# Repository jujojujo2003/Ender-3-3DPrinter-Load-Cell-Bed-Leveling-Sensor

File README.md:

# Ender-3-3DPrinter-Load-Cell-Bed-Leveling-Sensor
 This is a Load Cell based bed leveling sensor that should mount onto any vertical MGN12H gantry
 It uses
 * [ADS1235 ADC](https://www.digikey.com/en/products/detail/texas-instruments/ADS1235QWRHMRQ1/11308865) due to its 24-bit ADC, 7.2k sampling rate, 128x PGA gain.
 * [RP2040 MCU](https://www.raspberrypi.com/products/rp2040/) to do all the processing
 * [500g TAL 221 Loadcell](https://cdn.sparkfun.com/assets/9/9/a/f/3/TAL221.pdf) due to its compact nature. My gantry weighs around 250g. So make sure to select appropriate loadcell based on your gantry's weight so as to not saturate the loadcell.

My 3d printer is an Ender-3 with [3dFused's linear rail kit](https://3dfused.com/product/xaxis235/) and it perfectly works with that.

## PCB

You can order this PCB on [OSHPark](https://oshpark.com/shared_projects/gbeaSpQu).
Alternatively, the KiCad Schematic is available on [github](https://github.com/jujojujo2003/MGN12H-3DPrinter-LoadCell-BedLevelingSensor/tree/main/PCB) and the [Digikey parts list here](https://github.com/jujojujo2003/MGN12H-3DPrinter-LoadCell-BedLevelingSensor/blob/main/PCB/LoadCellDigikeyParts.csv)

<TBD> Source code and mounting bracket

## Code

The Arduino IDE code is available [here](https://github.com/jujojujo2003/MGN12H-3DPrinter-LoadCell-BedLevelingSensor/tree/main/Code). 
* Install [Arduino IDE](https://www.arduino.cc/en/software)
* Install the following Arduino Libraries
  * [PioSPI](https://www.arduino.cc/reference/en/libraries/piospi/)
  * [Adafruit NeoPixel](https://www.arduino.cc/reference/en/libraries/adafruit-neopixel/)
  * [RunningAverage](https://www.arduino.cc/reference/en/libraries/runningaverage/)
* Try compiling the binary

Alternatively, you can flash the [precompiled binary](https://github.com/jujojujo2003/MGN12H-3DPrinter-LoadCell-BedLevelingSensor/releases/tag/release)

## Normal Operation

* If everything is wired correctly, as soon as you power on, the LED should be RED for a few seconds and then turn off. If it flashes red, then there is an error. Try connecting the USB port and check the debug message printed to serial. 

* When the sensor is probing, the LED should turn blue to indicate that it is probing and turn green for a short while when triggered.

## Tuning
[DELTA_FOR_TRIGGER](https://github.com/jujojujo2003/MGN12H-3DPrinter-LoadCell-BedLevelingSensor/blob/main/Code/bedlevelRp2040ADS1235.ino#L8) is the main tuning variable that controls the sensitivity of the probe.

* Typically, set DELTA_FOR_TRIGGER to a low value like 1-2 and set `is_probing = true`
* Reset your printer and as soon as it starts, the LED should be BLUE. Note that it might get triggers very easily and turn green since the threshold above is low.
* Keep the filament wire into the extruder tight and try to extrude filament or move the printer head and keep bumping up DELTA_FOR_TRIGGER till such motions don't trigger.
* Now the probe will only trigger for probing motions

## Z-Probe Repeatability Test

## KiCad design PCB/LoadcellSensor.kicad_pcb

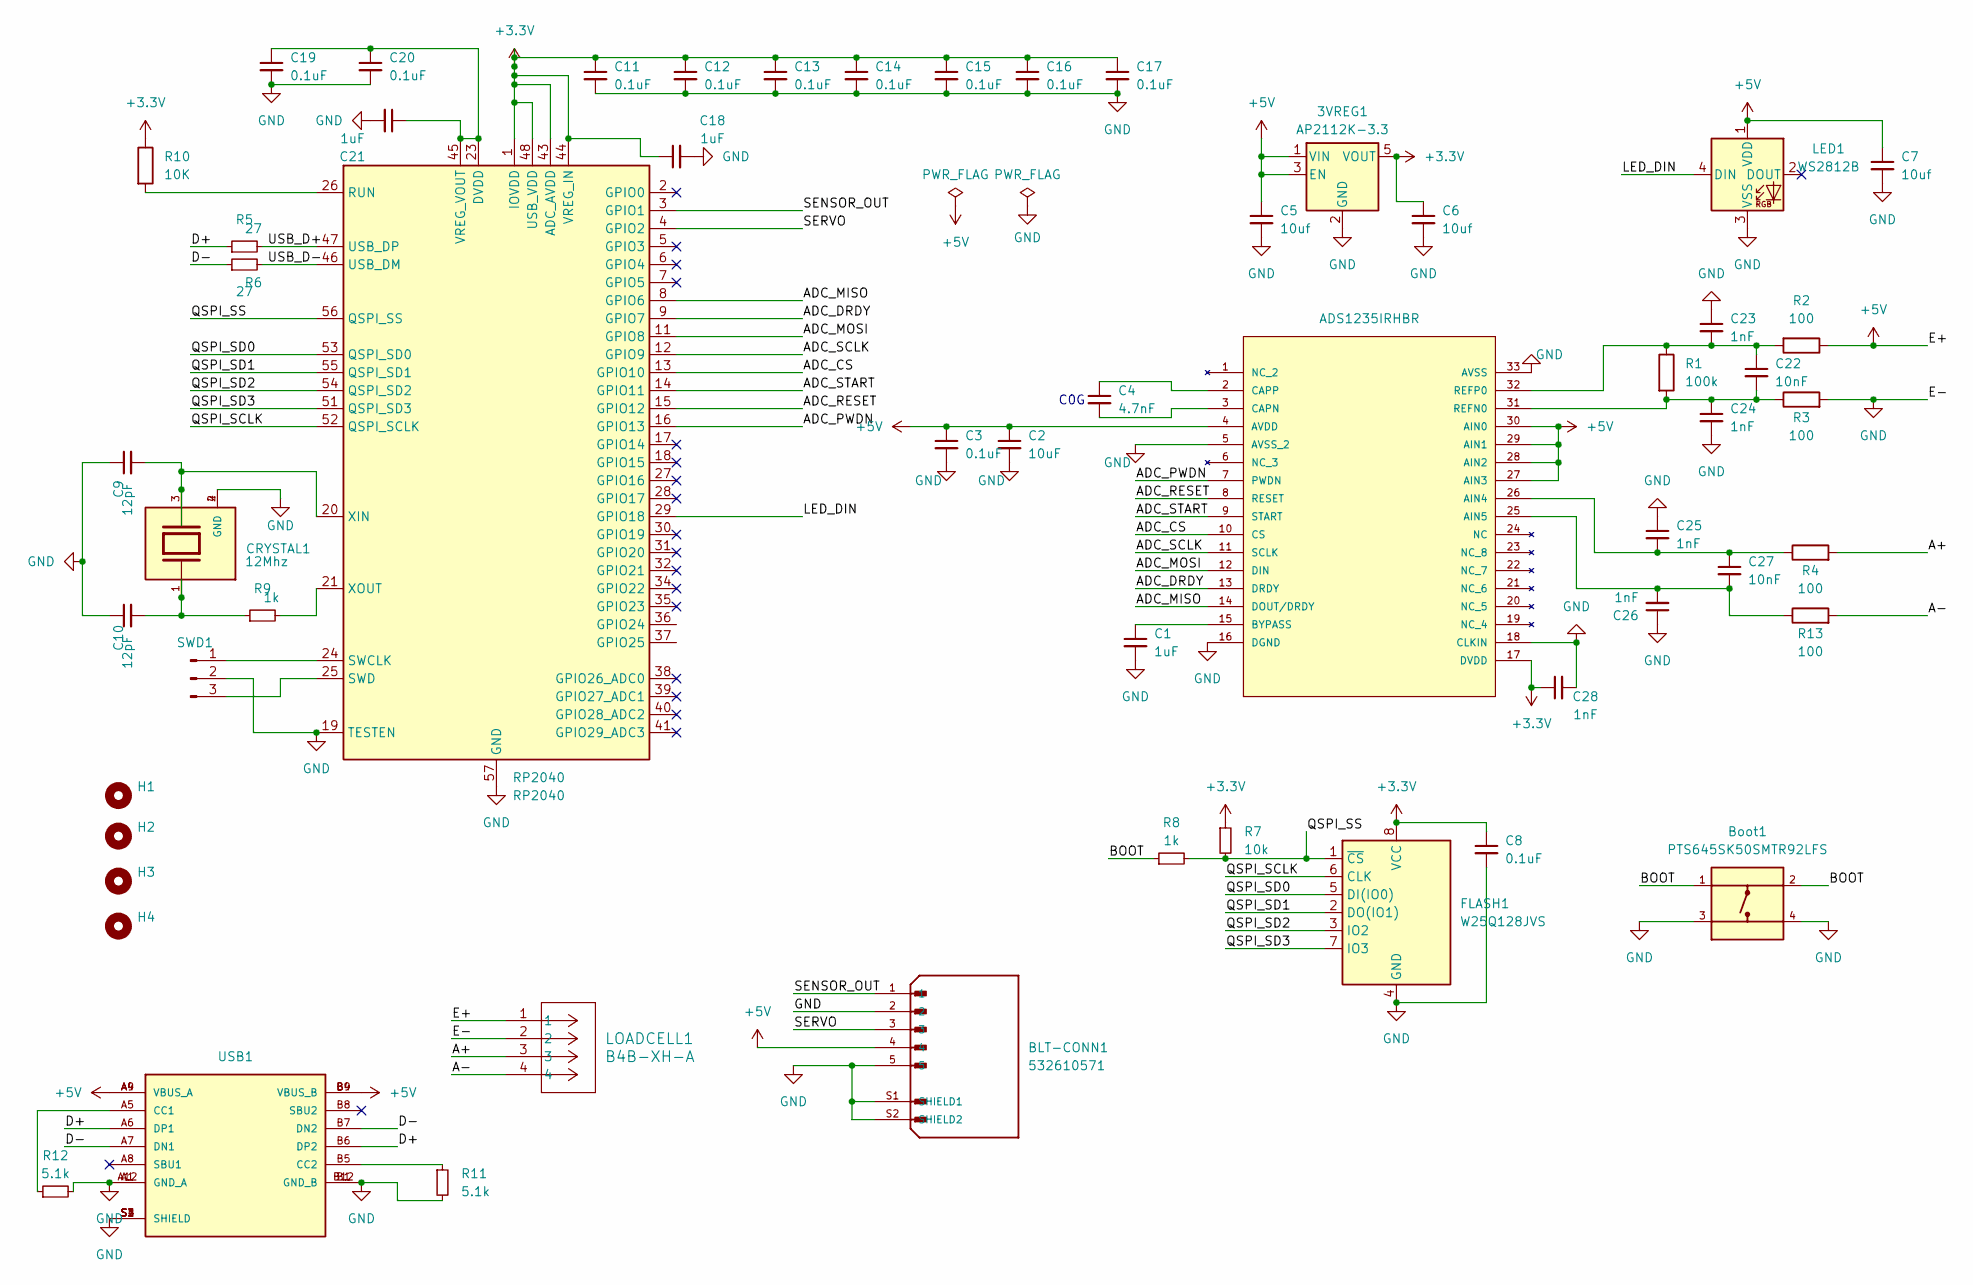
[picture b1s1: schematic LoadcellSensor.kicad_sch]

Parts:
3VREG1: AP2112K-3.3; SOT-23-5; DigiKey_Part_Number AP2112K-3.3TRG1DICT-ND
BLT-CONN1: 532610571; MOLEX_532610571; PARTREV J; DigiKey_Part_Number WM7623CT-ND
Boot1: PTS645SK50SMTR92LFS; SW_PTS645SK50SMTR92LFS; DigiKey_Part_Number CKN9087TR-ND
C1, C18, C21: 1uF; C_0805_2012Metric_Pad1.18x1.45mm_HandSolder; DigiKey_Part_Number 311-3498-1-ND
C2: 10uF; C_0805_2012Metric_Pad1.18x1.45mm_HandSolder; DigiKey_Part_Number 399-C0805C106J8RACAUTO7210CT-ND
C3, C8, C11, C12, C13, C14, C15, C16, C17, C19, C20: 0.1uF; C_0805_2012Metric_Pad1.18x1.45mm_HandSolder; DigiKey_Part_Number 311-1858-1-ND
C4: 4.7nF; C_0805_2012Metric_Pad1.18x1.45mm_HandSolder; DigiKey_Part_Number 399-C0805C472F5GEC7800CT-ND
C5, C6, C7: 10uf; C_0805_2012Metric_Pad1.18x1.45mm_HandSolder; DigiKey_Part_Number 399-C0805C106J8RACAUTO7210CT-ND
C9, C10: 12pF; C_0805_2012Metric_Pad1.18x1.45mm_HandSolder; DigiKey_Part_Number 399-C0805C120C5GAC7800CT-ND
C22, C27: 10nF; C_0805_2012Metric_Pad1.18x1.45mm_HandSolder; DigiKey_Part_Number 399-C0805C103J5GEC7800CT-ND
C23, C24, C25, C26, C28: 1nF; C_0805_2012Metric_Pad1.18x1.45mm_HandSolder; DigiKey_Part_Number 399-17883-1-ND
CRYSTAL1: 12Mhz; XTAL_ABM3B-12.000MHZ-12-N2Y-T; PARTREV 08.25.15; DigiKey_Part_Number 535-14827-1-ND
FLASH1: W25Q128JVS; SOIC-8_5.23x5.23mm_P1.27mm; DigiKey_Part_Number W25Q128JVSIQCT-ND
H1, H2, H3, H4: MountingHole; MountingHole_3.5mm
LED1: WS2812B; LED_WS2812B_PLCC4_5.0x5.0mm_P3.2mm; DigiKey_Part_Number WS2812B
LOADCELL1: B4B-XH-A; JST_XH_B4B-XH-A_1x04_P2.50mm_Vertical
R1: 100k; R_0805_2012Metric_Pad1.20x1.40mm_HandSolder; DigiKey_Part_Number 13-RC0805FR-13100KLCT-ND
R2, R3, R4, R13: 100; R_0805_2012Metric_Pad1.20x1.40mm_HandSolder; DigiKey_Part_Number 311-100CRCT-ND
R5, R6: 27; R_0805_2012Metric_Pad1.20x1.40mm_HandSolder; DigiKey_Part_Number 311-27.0CRCT-ND
R7: 10k; R_0805_2012Metric_Pad1.20x1.40mm_HandSolder; DigiKey_Part_Number 311-10.0KCRCT-ND
R8, R9: 1k; R_0805_2012Metric_Pad1.20x1.40mm_HandSolder; DigiKey_Part_Number 311-1.00KCRCT-ND
R10: 10K; R_0805_2012Metric_Pad1.20x1.40mm_HandSolder; DigiKey_Part_Number 311-10.0KCRCT-ND
R11, R12: 5.1k; R_0805_2012Metric_Pad1.20x1.40mm_HandSolder; DigiKey_Part_Number 311-5.10KCRCT-ND
RP2040: RP2040; QFN-56-1EP_7x7mm_P0.4mm_EP3.2x3.2mm; DigiKey_Part_Number 2648-SC0914(13)CT-ND
SWD1: JST_SH_SM03B-SRSS-TB_1x03-1MP_P1.00mm_Horizontal; DigiKey_Part_Number 455-SM03B-SRSS-TBCT-ND
U1: ADS1235IRHBR; VQFN32_5X5_TEX; MANUFACTURER_PART_NUMBER ADS1235IRHBR; DigiKey_Part_Number 296-ADS1235QWRHMRQ1CT-ND
USB1: GCT_USB4145-03-0170-C_REVA2; PARTREV A2; DigiKey_Part_Number 2073-USB4145-03-0170-CCT-ND

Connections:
+3.3V: 3VREG1.5 (VOUT), C6.1, C8.1, C11.1, C12.1, C13.1, C14.1, C15.1, C16.1, C17.1, C18.1, C28.1, FLASH1.8 (VCC), R7.1, R10.1, RP2040.1 (IOVDD), RP2040.10 (IOVDD), RP2040.22 (IOVDD), RP2040.33 (IOVDD), RP2040.42 (IOVDD), RP2040.43 (ADC_AVDD), RP2040.44 (VREG_IN), RP2040.48 (USB_VDD), RP2040.49 (IOVDD), U1.17 (DVDD)
+5V: 3VREG1.1 (VIN), 3VREG1.3 (EN), BLT-CONN1.4, C2.1, C3.1, C5.1, C7.1, LED1.1 (VDD), LOADCELL1.1, R2.1, U1.4 (AVDD), U1.27 (AIN3), U1.28 (AIN2), U1.29 (AIN1), U1.30 (AIN0), USB1.A4 (VBUS_A), USB1.A9 (VBUS_A), USB1.B4 (VBUS_B), USB1.B9 (VBUS_B)
/A+: LOADCELL1.3, R4.2
/A-: LOADCELL1.4, R13.2
/ADC_CS: RP2040.13 (GPIO10), U1.10 (CS)
/ADC_DRDY: RP2040.9 (GPIO7), U1.13 (DRDY)
/ADC_MISO: RP2040.8 (GPIO6), U1.14 (DOUT/DRDY)
/ADC_MOSI: RP2040.11 (GPIO8), U1.12 (DIN)
/ADC_PWDN: RP2040.16 (GPIO13), U1.7 (PWDN)
/ADC_RESET: RP2040.15 (GPIO12), U1.8 (RESET)
/ADC_SCLK: RP2040.12 (GPIO9), U1.11 (SCLK)
/ADC_START: RP2040.14 (GPIO11), U1.9 (START)
/BOOT: Boot1.1, Boot1.2, R8.1
/D+: R5.1, USB1.A6 (DP1), USB1.B6 (DP2)
/D-: R6.1, USB1.A7 (DN1), USB1.B7 (DN2)
/LED_DIN: LED1.4 (DIN), RP2040.29 (GPIO18)
/QSPI_SCLK: FLASH1.6 (CLK), RP2040.52 (QSPI_SCLK)
/QSPI_SD0: FLASH1.5 (DI(IO0)), RP2040.53 (QSPI_SD0)
/QSPI_SD1: FLASH1.2 (DO(IO1)), RP2040.55 (QSPI_SD1)
/QSPI_SD2: FLASH1.3 (IO2), RP2040.54 (QSPI_SD2)
/QSPI_SD3: FLASH1.7 (IO3), RP2040.51 (QSPI_SD3)
/QSPI_SS: FLASH1.1 (~CS), R7.2, R8.2, RP2040.56 (QSPI_SS)
/SENSOR_OUT: BLT-CONN1.1, RP2040.3 (GPIO1)
/SERVO: BLT-CONN1.3, RP2040.4 (GPIO2)
/USB_D+: R5.2, RP2040.47 (USB_DP)
/USB_D-: R6.2, RP2040.46 (USB_DM)
GND: 3VREG1.2 (GND), BLT-CONN1.2, BLT-CONN1.5, BLT-CONN1.S1 (SHIELD1), BLT-CONN1.S2 (SHIELD2), Boot1.3, Boot1.4, C1.2, C2.2, C3.2, C5.2, C6.2, C7.2, C8.2, C9.1, C10.1, C11.2, C12.2, C13.2, C14.2, C15.2, C16.2, C17.2, C18.2, C19.2, C20.2, C21.2, C23.1, C24.2, C25.1, C26.1, C28.2, CRYSTAL1.2 (GND), CRYSTAL1.4 (GND), FLASH1.4 (GND), LED1.3 (VSS), LOADCELL1.2, R3.2, R11.2, R12.2, RP2040.19 (TESTEN), RP2040.57 (GND), SWD1.2, U1.5 (AVSS_2), U1.16 (DGND), U1.18 (CLKIN), U1.33 (AVSS), USB1.A1 (GND_A), USB1.A12 (GND_A), USB1.B1 (GND_B), USB1.B12 (GND_B), USB1.S1 (SHIELD), USB1.S2 (SHIELD), USB1.S3 (SHIELD), USB1.S4 (SHIELD)
unnamed: C10.2, CRYSTAL1.1, R9.1
unnamed: R10.2, RP2040.26 (RUN)
unnamed: RP2040.24 (SWCLK), SWD1.1
unnamed: RP2040.25 (SWD), SWD1.3
unnamed: C19.1, C20.1, C21.1, RP2040.23 (DVDD), RP2040.45 (VREG_VOUT), RP2040.50 (DVDD)
unnamed: C9.2, CRYSTAL1.3, RP2040.20 (XIN)
unnamed: R9.2, RP2040.21 (XOUT)
unnamed: C25.2, C27.1, R4.1, U1.26 (AIN4)
unnamed: C26.2, C27.2, R13.1, U1.25 (AIN5)
unnamed: C1.1, U1.15 (BYPASS)
unnamed: C4.2, U1.3 (CAPN)
unnamed: C4.1, U1.2 (CAPP)
unnamed: C22.2, C24.1, R1.2, R3.1, U1.31 (REFN0)
unnamed: C22.1, C23.2, R1.1, R2.2, U1.32 (REFP0)
unnamed: R12.1, USB1.A5 (CC1)
unnamed: R11.1, USB1.B5 (CC2)

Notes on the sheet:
C0G

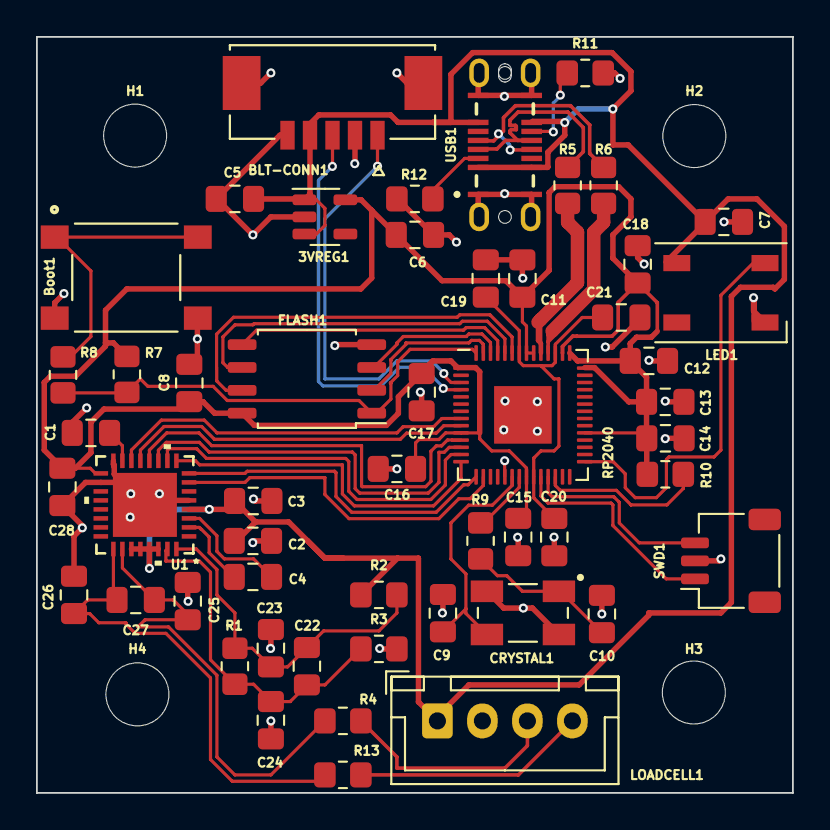
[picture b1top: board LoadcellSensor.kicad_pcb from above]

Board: 2 copper layers, 42.0 x 42.0 mm, 56 parts (0 on the bottom side), 43 nets.

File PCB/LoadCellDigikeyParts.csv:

"Reference","Value","Footprint","Datasheet","DigiKey_Part_Number","Qty"
"3VREG1","AP2112K-3.3","Package_TO_SOT_SMD:SOT-23-5","https://www.diodes.com/assets/Datasheets/AP2112.pdf","AP2112K-3.3TRG1DICT-ND","1"
"BLT-CONN1","532610571","MolexPicoBlade:MOLEX_532610571","","WM7623CT-ND","1"
"Boot1","PTS645SK50SMTR92LFS","PushButton:SW_PTS645SK50SMTR92LFS","","CKN9087TR-ND","1"
"C1, C18, C21","1uF","Capacitor_SMD:C_0805_2012Metric_Pad1.18x1.45mm_HandSolder","~","311-3498-1-ND","3"
"C2","10uF","Capacitor_SMD:C_0805_2012Metric_Pad1.18x1.45mm_HandSolder","~","399-C0805C106J8RACAUTO7210CT-ND","1"
"C3, C8, C11-C17, C19, C20","0.1uF","Capacitor_SMD:C_0805_2012Metric_Pad1.18x1.45mm_HandSolder","~","311-1858-1-ND","11"
"C4","4.7nF","Capacitor_SMD:C_0805_2012Metric_Pad1.18x1.45mm_HandSolder","~","399-C0805C472F5GEC7800CT-ND","1"
"C5-C7","10uf","Capacitor_SMD:C_0805_2012Metric_Pad1.18x1.45mm_HandSolder","~","399-C0805C106J8RACAUTO7210CT-ND","3"
"C9, C10","12pF","Capacitor_SMD:C_0805_2012Metric_Pad1.18x1.45mm_HandSolder","~","399-C0805C120C5GAC7800CT-ND","2"
"C22, C27","10nF","Capacitor_SMD:C_0805_2012Metric_Pad1.18x1.45mm_HandSolder","~","399-C0805C103J5GEC7800CT-ND","2"
"C23-C26, C28","1nF","Capacitor_SMD:C_0805_2012Metric_Pad1.18x1.45mm_HandSolder","~","399-17883-1-ND","5"
"CRYSTAL1","12Mhz","ABM3B-12.000MHZ-12-N2Y-T:XTAL_ABM3B-12.000MHZ-12-N2Y-T","","535-14827-1-ND","1"
"FLASH1","W25Q128JVS","Package_SO:SOIC-8_5.23x5.23mm_P1.27mm","http://www.winbond.com/resource-files/w25q128jv_dtr%20revc%2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","W25Q128JVSIQCT-ND","1"
"H1-H4","MountingHole","MountingHole:MountingHole_3.5mm","~","","4"
"LED1","WS2812B","LED_SMD:LED_WS2812B_PLCC4_5.0x5.0mm_P3.2mm","https://cdn-shop.adafruit.com/datasheets/WS2812B.pdf","WS2812B","1"
"LOADCELL1","B4B-XH-A","Connector_JST:JST_XH_B4B-XH-A_1x04_P2.50mm_Vertical","","","1"
"R1","100k","Resistor_SMD:R_0805_2012Metric_Pad1.20x1.40mm_HandSolder","~","13-RC0805FR-13100KLCT-ND","1"
"R2-R4, R13","100","Resistor_SMD:R_0805_2012Metric_Pad1.20x1.40mm_HandSolder","~","311-100CRCT-ND","4"
"R5, R6","27","Resistor_SMD:R_0805_2012Metric_Pad1.20x1.40mm_HandSolder","~","311-27.0CRCT-ND","2"
"R7","10k","Resistor_SMD:R_0805_2012Metric_Pad1.20x1.40mm_HandSolder","~","311-10.0KCRCT-ND","1"
"R8, R9","1k","Resistor_SMD:R_0805_2012Metric_Pad1.20x1.40mm_HandSolder","~","311-1.00KCRCT-ND","2"
"R10","10K","Resistor_SMD:R_0805_2012Metric_Pad1.20x1.40mm_HandSolder","~","311-10.0KCRCT-ND","1"
"R11, R12","5.1k","Resistor_SMD:R_0805_2012Metric_Pad1.20x1.40mm_HandSolder","~","311-5.10KCRCT-ND","2"
"RP2040","RP2040","Package_DFN_QFN:QFN-56-1EP_7x7mm_P0.4mm_EP3.2x3.2mm","https://datasheets.raspberrypi.com/rp2040/rp2040-datasheet.pdf","2648-SC0914(13)CT-ND","1"
"SWD1","~","Connector_JST:JST_SH_SM03B-SRSS-TB_1x03-1MP_P1.00mm_Horizontal","~","455-SM03B-SRSS-TBCT-ND","1"
"U1","ADS1235IRHBR","ADS1235IRHBR:VQFN32_5X5_TEX","","296-ADS1235QWRHMRQ1CT-ND","1"
"USB1","~","USB4145-03-0170-C_REVA2:GCT_USB4145-03-0170-C_REVA2","","2073-USB4145-03-0170-CCT-ND","1"

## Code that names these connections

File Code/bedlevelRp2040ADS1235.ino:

#include <SPI.h>
#include "PioSPI.h"
#include "ADS1235.h"
#include <Adafruit_NeoPixel.h>

//==================Config Variables========================
// Percentage of deviation allowed before probe trigger signal is sent
#define DELTA_FOR_TRIGGER 5

// Required target accuracy in mm for sensor
#define TARGET_ACCURACY 0.001 

// Probing speed in mm/min
#define PROBING_SPEED 30

// Number of samples to read to check if stable value is achieved
#define SAMPLES_FOR_STABILIZATION 10

// Relative percentage value before sample deemed stable. Value of one means wait for all samples to be ±1%
#define TOLERANCE_FOR_STABILIZATION 0.5

// How many ms to wait before fetching next sample
#define STABILIZATION_SAMPLING_INTERVAL_IN_MS 100

// ADS sampling speed
#define ADS_SPEED ADS1235::DataRate::SPS_7200

//===========================END============================

// ADC Pins
#define ADC_MISO 6
#define ADC_NOT_DRDY 7
#define ADC_MOSI 8
#define ADC_SCLK 9
#define ADC_CS 10
#define ADC_START 11
#define ADC_NOT_RESET 12
#define ADC_NOT_PWDN 13

// MCU PINS
#define LED_DIN 18
#define CONTROL_PIN 2
#define OUTPUT_PIN 1

PioSPI spiBus(ADC_MOSI, ADC_MISO, ADC_SCLK, ADC_CS, SPI_MODE1, 20000000);
SPISettings spiSettings(20000000, MSBFIRST, SPI_MODE1);
Adafruit_NeoPixel led(1, LED_DIN, NEO_GRB + NEO_KHZ800);

// State variables
uint64_t ledEndTime = 0;
uint32_t ledColor = 0;
bool is_probing = false;
unsigned long interruptRisingEdgeTime = 0;
uint16_t numberOfSamplesForProbing = 1; 

void halt(String reason) {
  unsigned long int start = millis();
  while ((millis()-start)<=2000) {
    if (micros() % 1000 == 0) {
      Serial.print("Halted: ");
      Serial.println(reason);
    }
    if ((millis() / 100) % 2 == 0) {
      led.fill(led.Color(255, 0, 0));
    } else {
      led.fill(led.Color(0, 0, 0));
    }
    led.show();
  }

  ADS1235::getInstance()->reset();
  NVIC_SystemReset();
}

void handleControlPinChange() {
  if (is_probing) {
    // If already probing, don't accept any more command
    return;
  }
  int input = digitalRead(CONTROL_PIN);
  if (input == HIGH) {
    interruptRisingEdgeTime = micros();
  } else {
    unsigned long int delta = micros() - interruptRisingEdgeTime;
    interruptRisingEdgeTime = 0;
    // BLTouch
    // https://youprintin3d.de/media/pdf/54/75/b4/f5a1c8_77037f55e5d542309d9fc178165c9f3f.pdf
    // Pin Down dutycycle 650us ±20 as per spec
    if (delta >= 620 && delta <= 680) {
      is_probing = true;
    }
  }
}

void updateLED() {
  if (is_probing) {
    led.fill(led.Color(0, 0, 255));
    led.show();
  } else if (ledEndTime == 0) {
    // Nothing to  do
  } else if (millis() < ledEndTime) {
    // Show color
    led.fill(ledColor);
    led.show();
  } else {
    // Clear LED reset state
    ledEndTime = 0;
    led.clear();
    led.show();
  }
}

void setLEDAndClearAfter(uint64_t duration_millis, uint32_t color) {
  ledEndTime = millis() + duration_millis;
  ledColor = color;
  updateLED();
}

void trigger() {
  digitalWrite(OUTPUT_PIN, HIGH);
  setLEDAndClearAfter(1000, led.Color(0, 255, 0));
  Serial.println("Triggered");
  delay(10);
  digitalWrite(OUTPUT_PIN, LOW);
}

double getNormalizedReadingFromADC() {
  return ADS1235::getInstance()->getRunningAverage()->getAverageLast(numberOfSamplesForProbing) * 100.0 / ADS1235::getInstance()->getRunningAverage()->getAverage();
}

void setup() {
  Serial.begin(115200);
  Serial.println("Inititalizing");
  
  pinMode(OUTPUT_PIN, OUTPUT);
  digitalWrite(OUTPUT_PIN, LOW);
  pinMode(CONTROL_PIN, INPUT_PULLUP);

  led.fill(led.Color(0, 0, 0));
  led.show();

  spiBus.begin();
  ADS1235::createInstance(spiBus, spiSettings, ADC_NOT_RESET, ADC_NOT_PWDN, ADC_START, ADC_NOT_DRDY);
  ADS1235::getInstance()->init();
  ADS1235::getInstance()->setInputMux(ADS1235::InputMux::AIN4, ADS1235::InputMux::AIN5);
  ADS1235::getInstance()->setDataRate(ADS_SPEED);
  ADS1235::getInstance()->setMode(ADS1235::ADCMode::NORMAL);
  ADS1235::getInstance()->caliberate();

  led.fill(led.Color(255, 0, 0));
  led.show();
  // Wait for buffer to fill
  while(!ADS1235::getInstance()->getRunningAverage()->bufferIsFull());
  led.fill(led.Color(255, 80, 0));
  led.show();

  // Verify settings
  if (ADS1235::getInstance()->getDataRate() != ADS_SPEED) {
    halt("Incorrect Datarate!");
  }

  if (ADS1235::getInstance()->getPositiveInputMux() != ADS1235::InputMux::AIN4) {
    halt("Incorrect Positive mux!");
  }

  if (ADS1235::getInstance()->getNegativeInputMux() != ADS1235::InputMux::AIN5) {
    halt("Incorrect Negative mux!");
  }

  if (ADS1235::getInstance()->getMode() != ADS1235::ADCMode::NORMAL) {
    halt("Incorrect MODE!");
  }

  // Make real time sampling data rate is roughtly same as what we set on initialization
  double dataRateRatio = (ADS1235::getInstance()->getRealDataRateAsInt()*1.0/ADS1235::getInstance()->getDataRateAsInt());
  if (dataRateRatio > 1.1 || dataRateRatio < 0.9) {
    halt("Realtime data rate not the same as what was set. Please check ADC connections");
  }

  // Samples to average for probing is number of samples that can fit in the time probe takes to travel TARGET_ACCURACY distance with PROBING_SPEED
  numberOfSamplesForProbing = ceil(ADS1235::getInstance()->getRealDataRateAsInt()*(TARGET_ACCURACY/(PROBING_SPEED/60.0)));
  if (numberOfSamplesForProbing < 1) {
    halt("numberOfSamplesForProbing < 1 . Your sensor is not capable of hitting the target accuracy given the probing speed. Try changing either of them");
  }

  // Setup Interupts
  attachInterrupt(CONTROL_PIN, handleControlPinChange, CHANGE);

  // Wait for data to stabilize
  // Fetch data at 100 ms intervals and wait for all 10 sample points to be ± 1 of avg value 
  double data[SAMPLES_FOR_STABILIZATION];
  uint8_t last_ptr = 0;
  while(last_ptr<SAMPLES_FOR_STABILIZATION){
    data[last_ptr] = getNormalizedReadingFromADC();
    delay(STABILIZATION_SAMPLING_INTERVAL_IN_MS);
    last_ptr++;
  }
  bool has_stabilized = true;
  do {
    has_stabilized = true;
    for(int i=0;i<SAMPLES_FOR_STABILIZATION;i++) {
      if (data[i] > (100+TOLERANCE_FOR_STABILIZATION) || data[i] < (100-TOLERANCE_FOR_STABILIZATION)) {
        // Data not stable
        has_stabilized = false;
        // get next value
        last_ptr = (last_ptr+1)%SAMPLES_FOR_STABILIZATION;
        data[last_ptr]  = getNormalizedReadingFromADC();
        led.fill(led.Color(255*((millis()/100)%2), 80*((millis()/100)%2), 0));
        led.show();
        delay(STABILIZATION_SAMPLING_INTERVAL_IN_MS);
        break;
      }
    }
  } while(!has_stabilized);
  led.fill(led.Color(0, 255, 0));
  led.show();
  delay(1000);
  led.fill(led.Color(0, 0, 0));
  led.show();
}

void loop() {
  updateLED();
  // Uncomment for debug logs
  /*if (micros()%100000 ==0) {
    Serial.print(ADS1235::getInstance()->getRealDataRateAsInt());
    Serial.print(" ");
    Serial.print(numberOfSamplesForProbing);
    Serial.print(" ");
    Serial.print(getNormalizedReadingFromADC());
    Serial.println();
  }*/
  if (is_probing) {
    double normalizedValue = getNormalizedReadingFromADC();
    if (normalizedValue <= (100 - DELTA_FOR_TRIGGER) || normalizedValue >= (100 + DELTA_FOR_TRIGGER)) {
      // Probing  done
      // Reset state variables
      is_probing = false;
      trigger();
    }
  }
}

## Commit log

2024-03-30 PCB commit
2024-05-07 Add code
2024-05-07 Add STL
2024-05-07 assets
2024-08-11 Add averaging for probing as well

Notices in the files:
parts and their libraries:
COPYRIGHT: Copyright (C) 2021 Ultra Librarian. All rights reserved.
